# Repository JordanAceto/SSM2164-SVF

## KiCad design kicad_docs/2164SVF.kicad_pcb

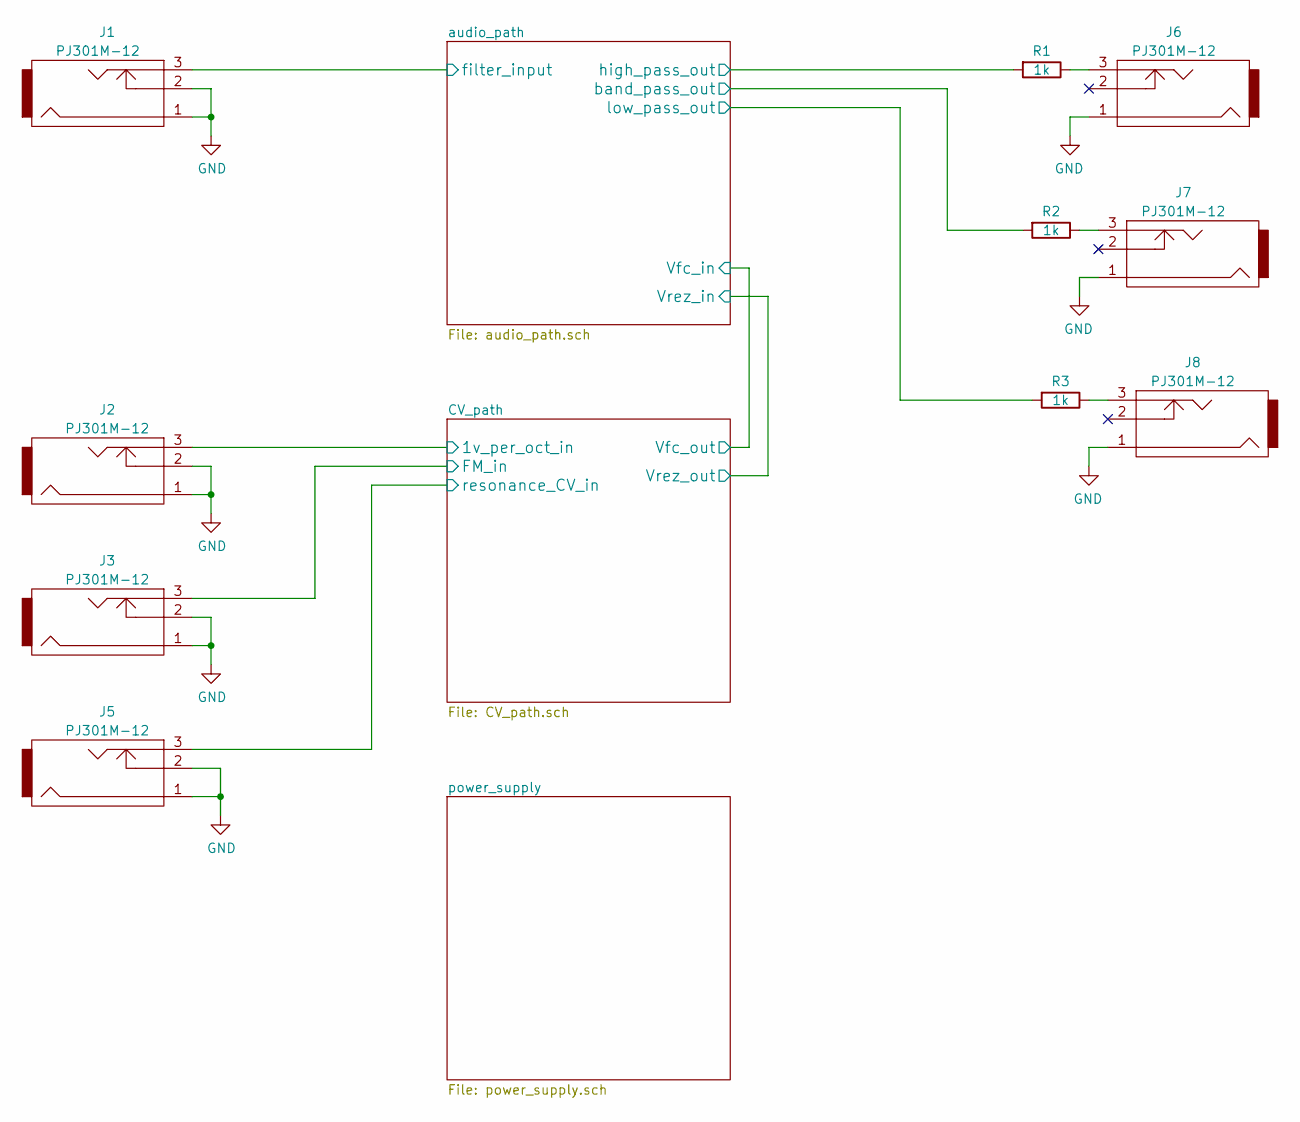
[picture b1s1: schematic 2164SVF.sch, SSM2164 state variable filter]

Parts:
J1, J2, J3, J5, J6, J7, J8: PJ301M-12
R1, R2, R3: 1k; R_0805_2012Metric_Pad1.15x1.40mm_HandSolder

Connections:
/CV_path/1v_per_oct_in: J2.3; also elsewhere on the board
/CV_path/FM_in: J3.3; also elsewhere on the board
/CV_path/resonance_CV_in: J5.3; also elsewhere on the board
/audio_path/band_pass_out: R2.2; also elsewhere on the board
/audio_path/filter_input: J1.3; also elsewhere on the board
/audio_path/high_pass_out: R1.2; also elsewhere on the board
/audio_path/low_pass_out: R3.2; also elsewhere on the board
GND: J1.1, J1.2, J2.1, J2.2, J3.1, J3.2, J5.1, J5.2, J6.1, J7.1, J8.1; also elsewhere on the board
unnamed: J6.3, R1.1
unnamed: J7.3, R2.1
unnamed: J8.3, R3.1

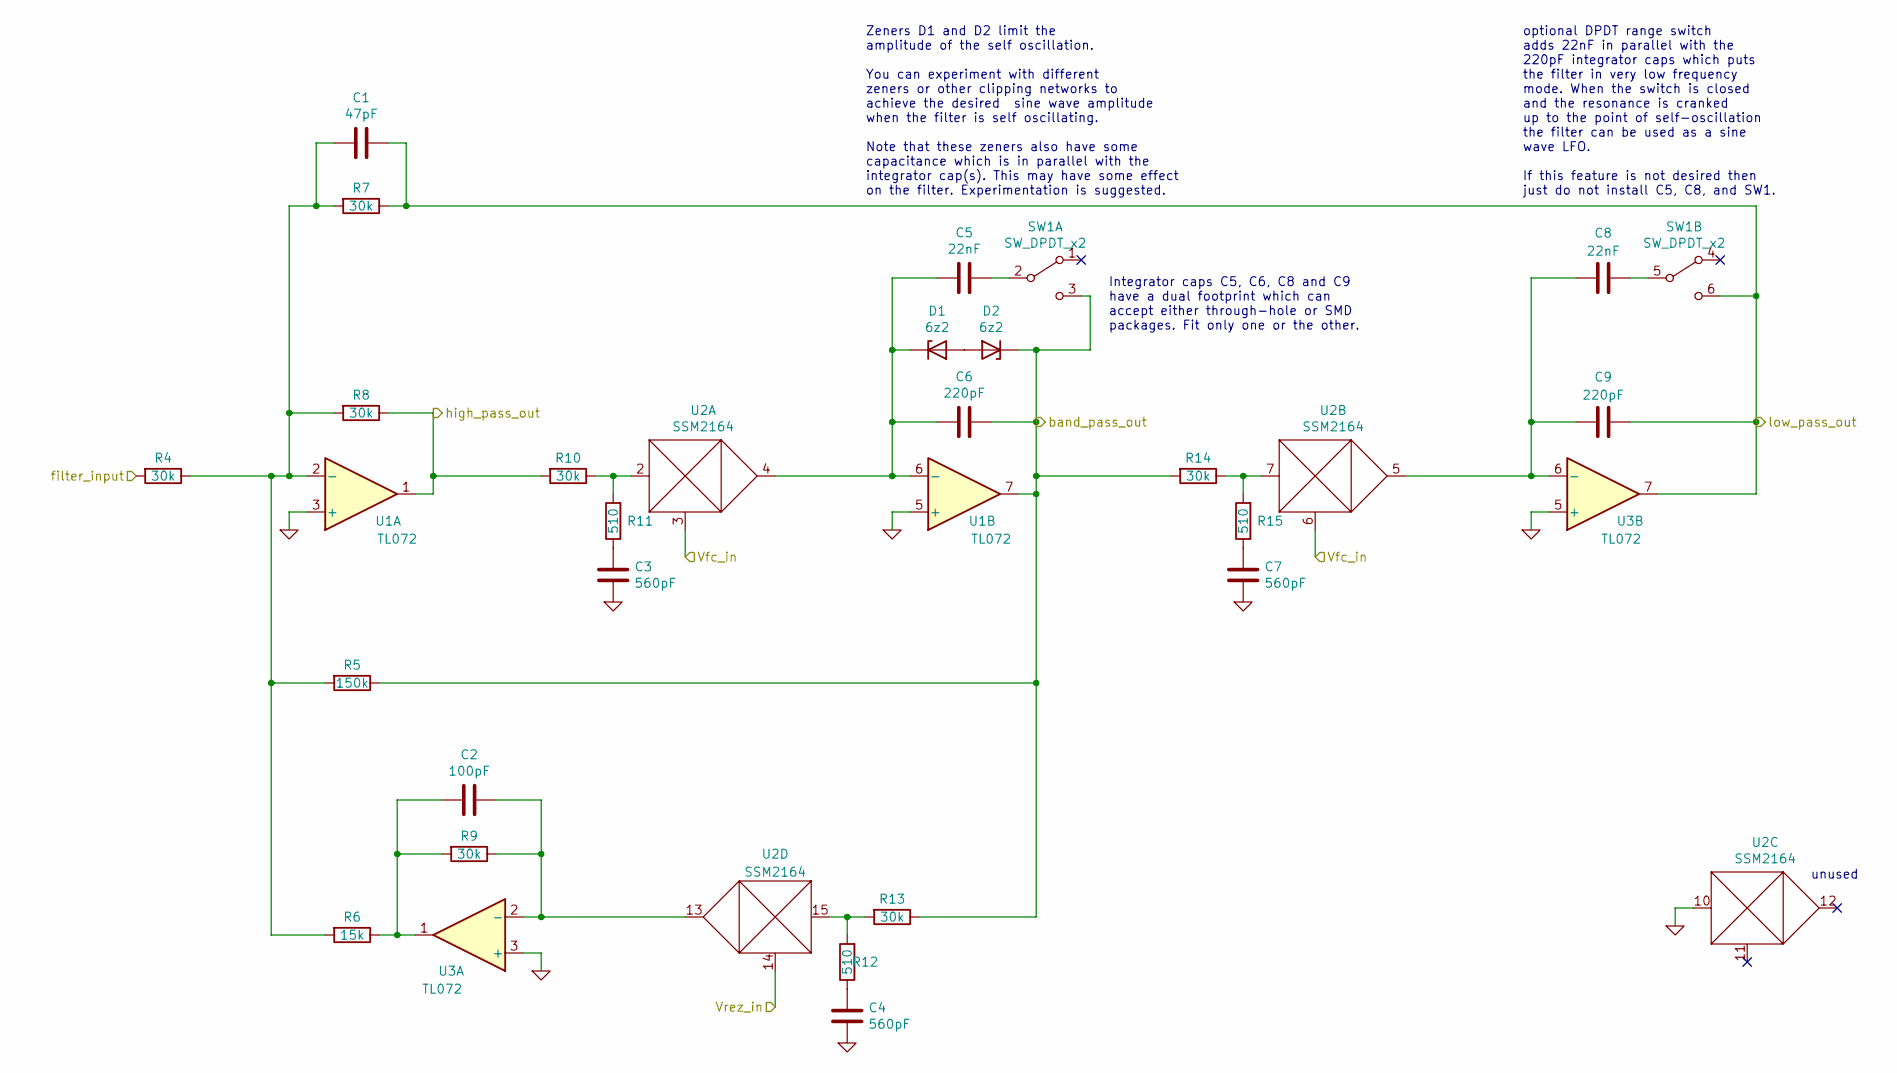
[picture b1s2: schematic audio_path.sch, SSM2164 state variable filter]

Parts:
C1: 47pF; C_0805_2012Metric_Pad1.15x1.40mm_HandSolder
C2: 100pF; C_0805_2012Metric_Pad1.15x1.40mm_HandSolder
C3, C4, C7: 560pF; C_0805_2012Metric_Pad1.15x1.40mm_HandSolder
C5, C8: 22nF; timing_cap_dual_fp
C6, C9: 220pF; timing_cap_dual_fp
D1, D2: 6z2; D_SOD-123
R4, R7, R8, R9, R10, R13, R14: 30k; R_0805_2012Metric_Pad1.15x1.40mm_HandSolder
R5: 150k; R_0805_2012Metric_Pad1.15x1.40mm_HandSolder
R6: 15k; R_0805_2012Metric_Pad1.15x1.40mm_HandSolder
R11, R12, R15: 510; R_0805_2012Metric_Pad1.15x1.40mm_HandSolder
SW1: SW_DPDT_x2; DPDT_on_on
U1, U3: TL072; SOIC-8_3.9x4.9mm_P1.27mm
U2: SSM2164; SOIC-16_3.9x9.9mm_P1.27mm

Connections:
/audio_path/Vfc_in: U2.3, U2.6; also elsewhere on the board
/audio_path/Vrez_in: U2.14; also elsewhere on the board
/audio_path/band_pass_out: C6.1, D2.1 (K), R5.1, R13.1, R14.2, SW1.3 (C), U1.7; also elsewhere on the board
/audio_path/filter_input: R4.2; also elsewhere on the board
/audio_path/high_pass_out: R8.1, R10.2, U1.1; also elsewhere on the board
/audio_path/low_pass_out: C1.1, C9.1, R7.1, SW1.6 (C), U3.7; also elsewhere on the board
GND: C3.2, C4.2, C7.2, U1.3 (+), U1.5 (+), U2.10, U3.3 (+), U3.5 (+); also elsewhere on the board
unnamed: C1.2, R4.1, R5.2, R6.2, R7.2, R8.2, U1.2 (-)
unnamed: C2.1, R9.1, U2.13, U3.2 (-)
unnamed: C2.2, R6.1, R9.2, U3.1
unnamed: C3.1, R11.1
unnamed: C4.1, R12.1
unnamed: C5.1, SW1.2 (B)
unnamed: C5.2, C6.2, D1.1 (K), U1.6 (-), U2.4
unnamed: C7.1, R15.1
unnamed: C8.1, SW1.5 (B)
unnamed: C8.2, C9.2, U2.5, U3.6 (-)
unnamed: D1.2 (A), D2.2 (A)
unnamed: R10.1, R11.2, U2.2
unnamed: R12.2, R13.2, U2.15
unnamed: R14.1, R15.2, U2.7

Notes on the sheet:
optional DPDT range switch adds 22nF in parallel with the 220pF integrator caps which puts the filter in very low frequency mode. When the switch is closed and the resonance is cranked up to the point of self-oscillation the filter can be used as a sine wave LFO. If this feature is not desired then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
unused
Integrator caps C5, C6, C8 and C9 have a dual footprint which can accept either through-hole or SMD packages. Fit only one or the other.
Zeners D1 and D2 limit the amplitude of the self oscillation. You can experiment with different zeners or other clipping networks to achieve the desired sine wave amplitude when the filter is self oscillating. Note that these zeners also have some capacitance which is in parallel with the integrato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

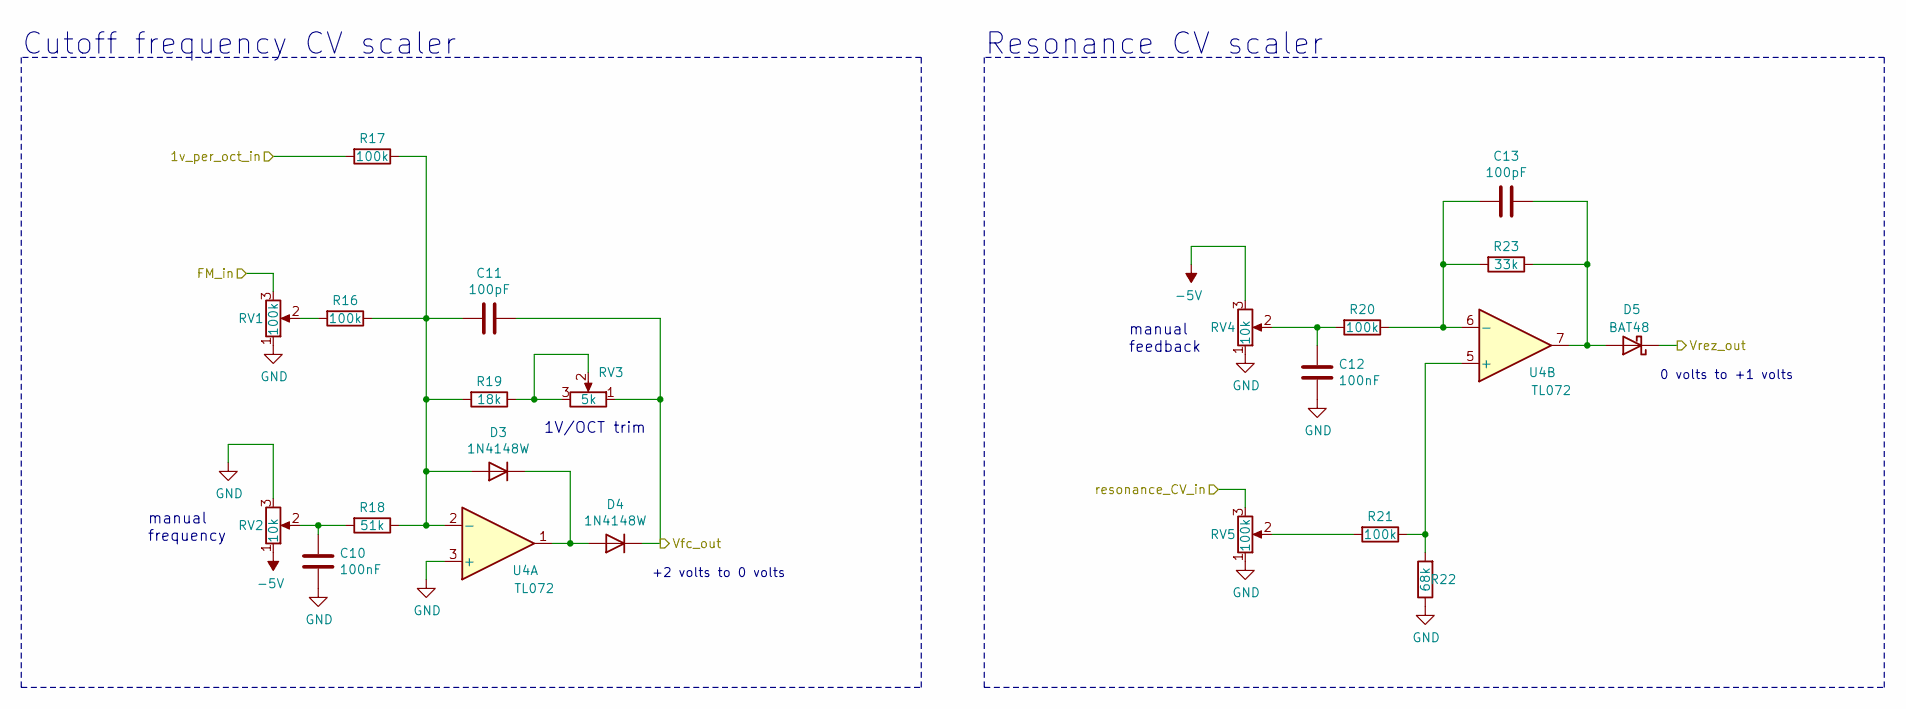
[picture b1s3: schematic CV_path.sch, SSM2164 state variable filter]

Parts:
C10, C12: 100nF; C_0805_2012Metric_Pad1.15x1.40mm_HandSolder
C11, C13: 100pF; C_0805_2012Metric_Pad1.15x1.40mm_HandSolder
D3, D4: 1N4148W; D_SOD-123
D5: BAT48; D_SOD-123
R16, R17, R20, R21: 100k; R_0805_2012Metric_Pad1.15x1.40mm_HandSolder
R18: 51k; R_0805_2012Metric_Pad1.15x1.40mm_HandSolder
R19: 18k; R_0805_2012Metric_Pad1.15x1.40mm_HandSolder
R22: 68k; R_0805_2012Metric_Pad1.15x1.40mm_HandSolder
R23: 33k; R_0805_2012Metric_Pad1.15x1.40mm_HandSolder
RV1, RV5: 100k; Potentiometer_Alpha_RD901F-40-00D_Single_Vertical
RV2, RV4: 10k; Potentiometer_Alpha_RD901F-40-00D_Single_Vertical
RV3: 5k; Potentiometer_Bourns_3296W_Vertical
U4: TL072; SOIC-8_3.9x4.9mm_P1.27mm

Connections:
-5V: RV2.1, RV4.3; also elsewhere on the board
/CV_path/1v_per_oct_in: R17.2; also elsewhere on the board
/CV_path/FM_in: RV1.3; also elsewhere on the board
/CV_path/resonance_CV_in: RV5.3; also elsewhere on the board
/audio_path/Vfc_in: C11.1, D4.1 (K), RV3.1; also elsewhere on the board
/audio_path/Vrez_in: D5.1 (K); also elsewhere on the board
GND: C10.1, C12.1, R22.1, RV1.1, RV2.3, RV4.1, RV5.1, U4.3 (+); also elsewhere on the board
unnamed: C10.2, R18.2, RV2.2
unnamed: C11.2, D3.2 (A), R16.1, R17.1, R18.1, R19.2, U4.2 (-)
unnamed: C12.2, R20.2, RV4.2
unnamed: C13.1, D5.2 (A), R23.1, U4.7
unnamed: C13.2, R20.1, R23.2, U4.6 (-)
unnamed: D3.1 (K), D4.2 (A), U4.1
unnamed: R16.2, RV1.2
unnamed: R19.1, RV3.2, RV3.3
unnamed: R21.1, R22.2, U4.5 (+)
unnamed: R21.2, RV5.2

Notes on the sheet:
1V/OCT trim
manual frequency
manual feedback
Cutoff frequency CV scaler
Resonance CV scaler
0 volts to +1 volts
+2 volts to 0 volts

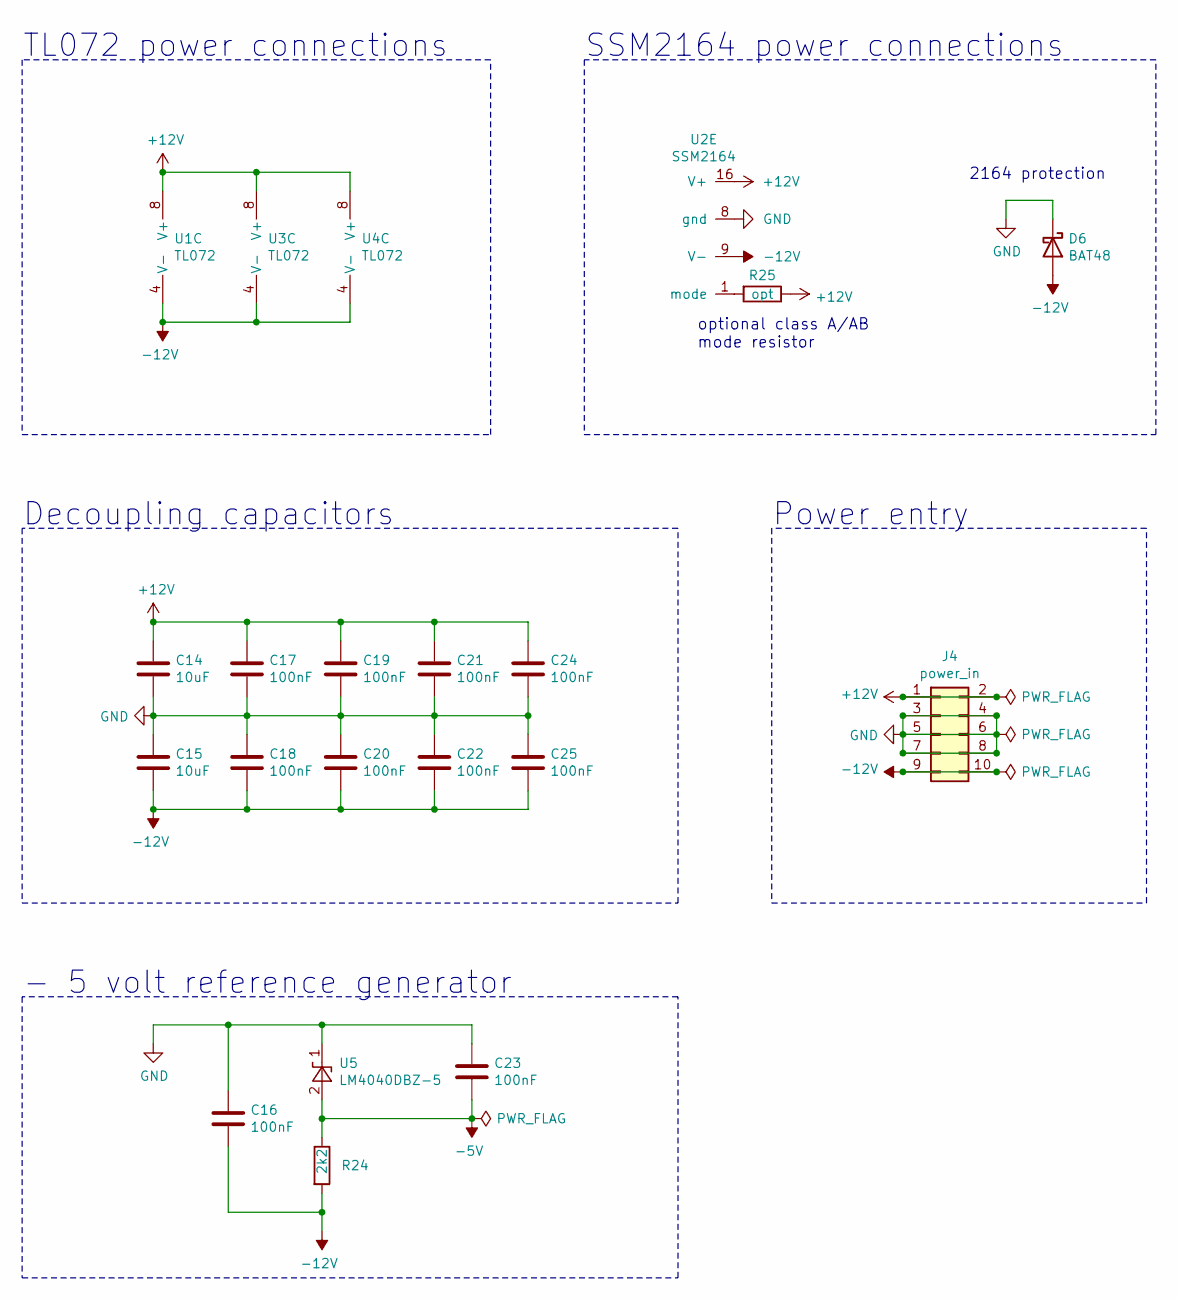
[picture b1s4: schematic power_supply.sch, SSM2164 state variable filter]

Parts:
C14, C15: 10uF; CP_Elec_6.3x5.4_Nichicon
C16, C17, C18, C19, C20, C21, C22, C23, C24, C25: 100nF; C_0805_2012Metric_Pad1.15x1.40mm_HandSolder
D6: BAT48; D_SOD-123
J4: power_in; PinHeader_2x05_P2.54mm_Vertical
R24: 2k2; R_0805_2012Metric_Pad1.15x1.40mm_HandSolder
R25: opt; R_0805_2012Metric_Pad1.15x1.40mm_HandSolder
U1, U3, U4: TL072; SOIC-8_3.9x4.9mm_P1.27mm
U2: SSM2164; SOIC-16_3.9x9.9mm_P1.27mm
U5: LM4040DBZ-5; SOT-23_Handsoldering

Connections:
+12V: C14.1, C17.1, C19.1, C21.1, C24.1, J4.1, J4.2, R25.1, U1.8 (V+), U2.16 (V+), U3.8 (V+), U4.8 (V+)
-5V: C23.2, R24.1, U5.2 (A); also elsewhere on the board
-12V: C15.2, C16.2, C18.2, C20.2, C22.2, C25.2, D6.2 (A), J4.9, J4.10, R24.2, U1.4 (V-), U2.9 (V-), U3.4 (V-), U4.4 (V-)
GND: C14.2, C15.1, C16.1, C17.2, C18.1, C19.2, C20.1, C21.2, C22.1, C23.1, C24.2, C25.1, D6.1 (K), J4.3, J4.4, J4.5, J4.6, J4.7, J4.8, U2.8 (gnd), U5.1 (K); also elsewhere on the board
unnamed: R25.2, U2.1 (mode)

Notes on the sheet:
2164 protection
optional class A/AB mode resistor
TL072 power connections
SSM2164 power connections
Decoupling capacitors
Power entry
- 5 volt reference generator

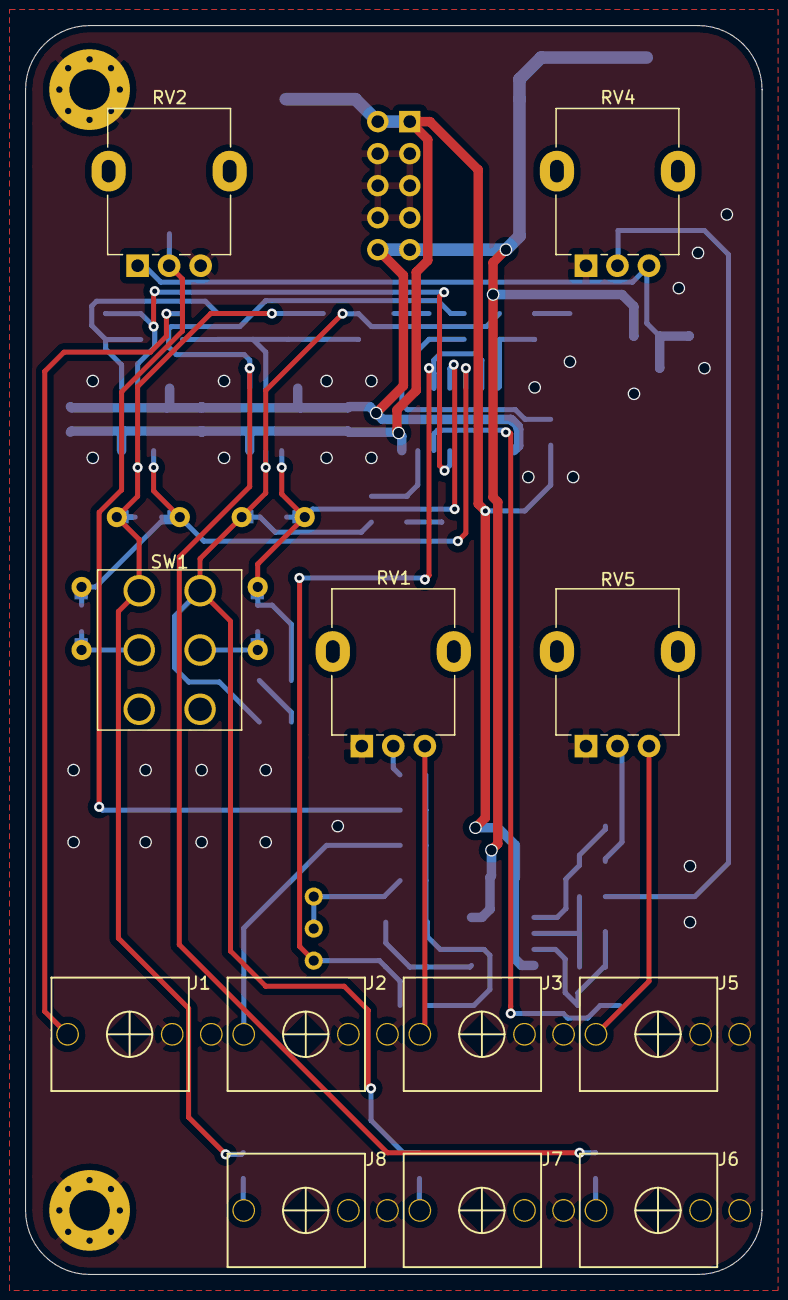
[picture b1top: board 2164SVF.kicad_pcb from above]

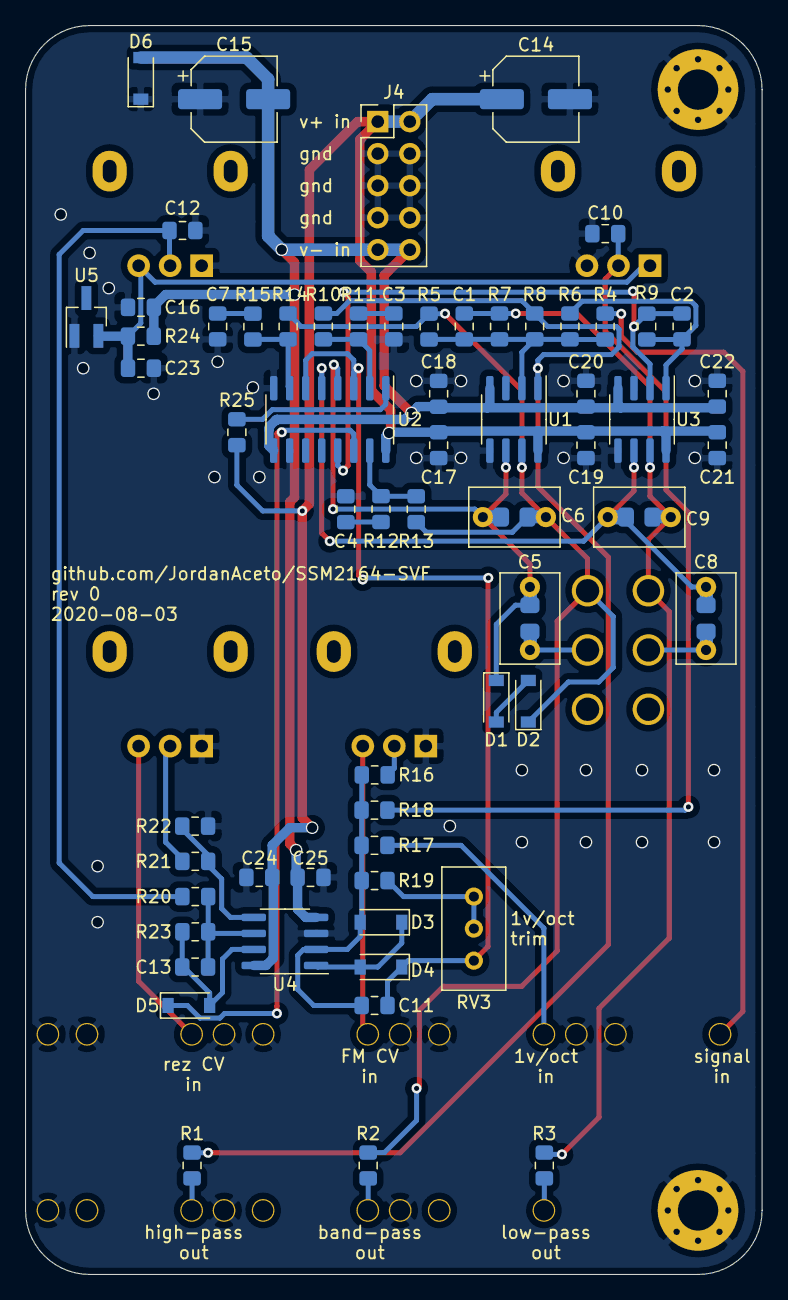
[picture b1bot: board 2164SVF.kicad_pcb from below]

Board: 2 copper layers, 58.4 x 99.1 mm, 77 parts (63 on the bottom side), 41 nets.

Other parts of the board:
H1, H2: MountingHole_Pad; MountingHole_3.2mm_M3_Pad_Via

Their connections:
GND: H1.1, H2.1; also elsewhere on the board

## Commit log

2018-09-01 add README
2018-09-01 add PDF of schematic
2020-07-31 big change, tidy schemo, update repo structure
2020-07-31 fix problem where jacks were all upside-down
2020-07-31 Create LICENSE
2020-08-03 first rev pcb layout
2020-08-03 update schematic
2020-08-03 generate interactive BOM
2020-08-03 add some rendered pcb pics
2020-11-28 built and tested, minor component changes
2021-05-25 add front panel, reorganize repo
2022-01-06 add finished pic, update readme
2022-01-06 front panel gerbers
2022-01-06 add link to schematic

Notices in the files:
kicad_docs/2164SVF.kicad_pcb:
License: CC by 4.0
kicad_docs/2164SVF.sch:
creativecommons.org/licenses/by/4.0
